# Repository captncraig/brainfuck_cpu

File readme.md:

### Main Control Signal Bus

0. CLK
1. PC_LD
2. PC_ST
3. IR_ST
4. DR_LD
5. DR_ST
6. DP_LD
7. DP_ST
8. INCREMENT_ON 
9. DECREMENT
10. ALU_LD
11. MAR_ST
12. MEM_LD
13. MEM_ST
14. MEM_PROG_DATA
15. 8Bit/16Bit

## Addional control signals

1. IO_OUT
2. IO_IN
3. IO_ACK

## FSM INPUTS

0. State0
1. State1
2. State2
3. State3
4. State4
5. DR_Z
6. IR0
7. IR1
8. IR2
9. IR_HI_Z
10. IR_LO_Z
11. RUN

## Additional FSM Outputs

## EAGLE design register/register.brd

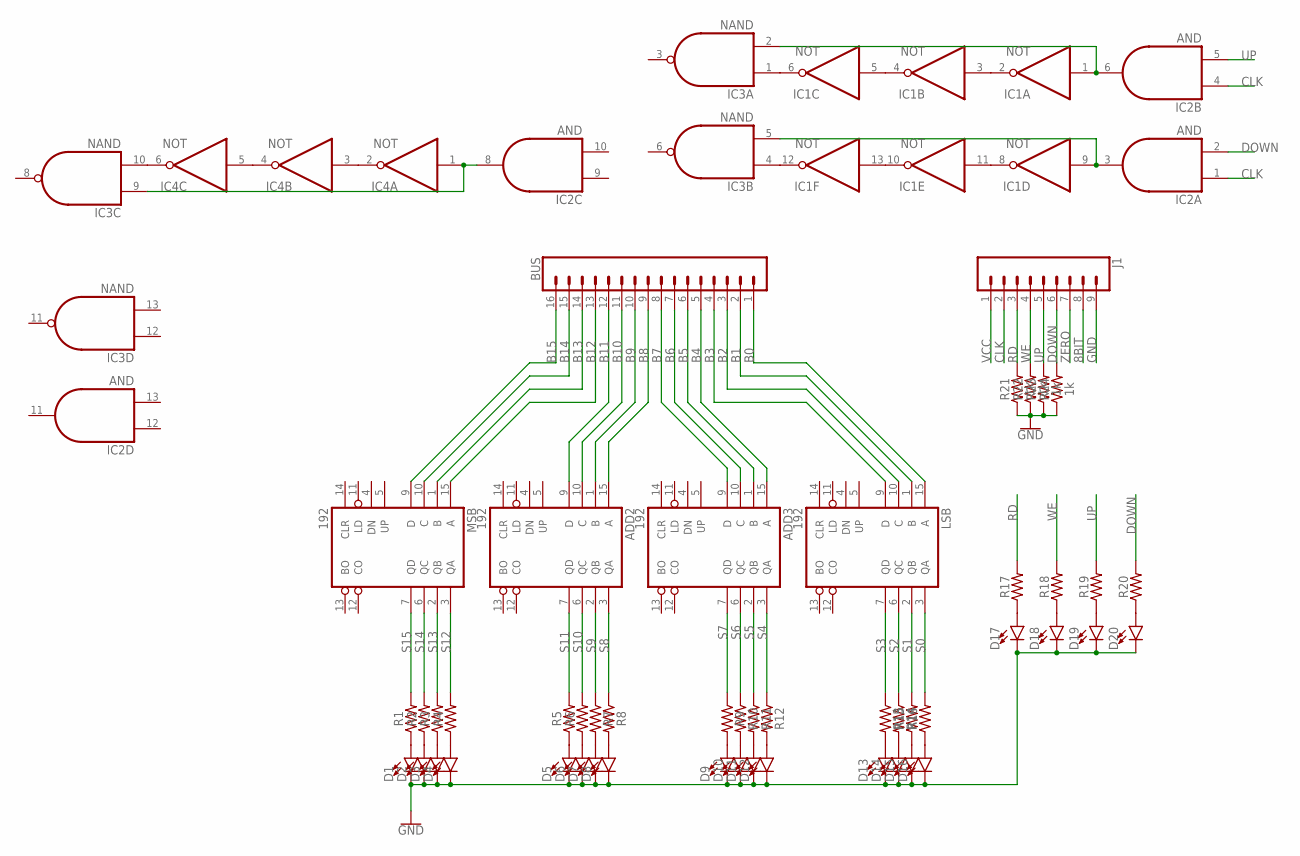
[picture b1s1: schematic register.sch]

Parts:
ADD2, ADD3: 192; DIL16
BUS: CONN_16; 1X16
D1, D2, D3, D4, D5, D6, D7, D8, D9, D10, D11, D12, D13, D14, D15, D16, D17, D18, D19, D20: LED5MM; LED_5MM
IC1, IC4: NOT; DIL14
IC2: AND; DIL14
IC3: NAND; DIL14
J1: CONN_09; 1X09
LSB: 192; DIL16
MSB: 192; DIL16
R1, R2, R3, R4, R5, R6, R7, R8, R9, R10, R11, R12, R13, R14, R15, R16, R17, R18, R19, R20: AXIAL-0.3
R21, R22, R23, R24: 1k; AXIAL-0.3

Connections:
8BIT: J1.8
B0: BUS.1, LSB.15 (A)
B1: BUS.2, LSB.1 (B)
B2: BUS.3, LSB.10 (C)
B3: BUS.4, LSB.9 (D)
B4: ADD3.15 (A), BUS.5
B5: ADD3.1 (B), BUS.6
B6: ADD3.10 (C), BUS.7
B7: ADD3.9 (D), BUS.8
B8: ADD2.15 (A), BUS.9
B9: ADD2.1 (B), BUS.10
B10: ADD2.10 (C), BUS.11
B11: ADD2.9 (D), BUS.12
B12: BUS.13, MSB.15 (A)
B13: BUS.14, MSB.1 (B)
B14: BUS.15, MSB.10 (C)
B15: BUS.16, MSB.9 (D)
CLK: IC2.1 (I0), IC2.4 (I0), J1.2
DOWN: IC2.2 (I1), J1.6, R20.P$2 (2), R24.P$2 (2)
GND: ADD2.8 (GND), ADD3.8 (GND), D1.K (C), D2.K (C), D3.K (C), D4.K (C), D5.K (C), D6.K (C), D7.K (C), D8.K (C), D9.K (C), D10.K (C), D11.K (C), D12.K (C), D13.K (C), D14.K (C), D15.K (C), D16.K (C), D17.K (C), D18.K (C), D19.K (C), D20.K (C), IC1.7 (GND), IC2.7 (GND), IC3.7 (GND), IC4.7 (GND), J1.9, LSB.8 (GND), MSB.8 (GND), R21.P$1 (1), R22.P$1 (1), R23.P$1 (1), R24.P$1 (1)
unnamed: IC1.2 (O), IC1.3 (I)
unnamed: IC1.4 (O), IC1.5 (I)
unnamed: IC1.8 (O), IC1.11 (I)
unnamed: IC1.10 (O), IC1.13 (I)
unnamed: IC1.9 (I), IC2.3 (O), IC3.5 (I1)
unnamed: IC1.1 (I), IC2.6 (O), IC3.2 (I1)
unnamed: IC1.6 (O), IC3.1 (I0)
unnamed: IC1.12 (O), IC3.4 (I0)
unnamed: IC4.2 (O), IC4.3 (I)
unnamed: IC4.4 (O), IC4.5 (I)
unnamed: IC2.8 (O), IC3.9 (I0), IC4.1 (I)
unnamed: IC3.10 (I1), IC4.6 (O)
unnamed: D1.A, R1.P$1 (1)
unnamed: D2.A, R2.P$1 (1)
unnamed: D3.A, R3.P$1 (1)
unnamed: D4.A, R4.P$1 (1)
unnamed: D5.A, R5.P$1 (1)
unnamed: D6.A, R6.P$1 (1)
unnamed: D7.A, R7.P$2 (2)
unnamed: D8.A, R8.P$2 (2)
unnamed: D9.A, R9.P$2 (2)
unnamed: D10.A, R10.P$2 (2)
unnamed: D11.A, R11.P$2 (2)
unnamed: D12.A, R12.P$2 (2)
unnamed: D13.A, R13.P$2 (2)
unnamed: D14.A, R14.P$2 (2)
unnamed: D15.A, R15.P$1 (1)
unnamed: D16.A, R16.P$1 (1)
unnamed: D18.A, R18.P$1 (1)
unnamed: D19.A, R19.P$1 (1)
unnamed: D20.A, R20.P$1 (1)
unnamed: D17.A, R17.P$1 (1)
RD: J1.3, R17.P$2 (2), R21.P$2 (2)
S0: LSB.3 (QA), R16.P$2 (2)
S1: LSB.2 (QB), R15.P$2 (2)
S2: LSB.6 (QC), R14.P$1 (1)
S3: LSB.7 (QD), R13.P$1 (1)
S4: ADD3.3 (QA), R12.P$1 (1)
S5: ADD3.2 (QB), R11.P$1 (1)
S6: ADD3.6 (QC), R10.P$1 (1)
S7: ADD3.7 (QD), R9.P$1 (1)
S8: ADD2.3 (QA), R8.P$1 (1)
S9: ADD2.2 (QB), R7.P$1 (1)
S10: ADD2.6 (QC), R6.P$2 (2)
S11: ADD2.7 (QD), R5.P$2 (2)
S12: MSB.3 (QA), R4.P$2 (2)
S13: MSB.2 (QB), R3.P$2 (2)
S14: MSB.6 (QC), R2.P$2 (2)
S15: MSB.7 (QD), R1.P$2 (2)
UP: IC2.5 (I1), J1.5, R19.P$2 (2), R23.P$2 (2)
VCC: ADD2.16 (VCC), ADD3.16 (VCC), IC1.14 (VCC), IC2.14 (VCC), IC3.14 (VCC), IC4.14 (VCC), J1.1, LSB.16 (VCC), MSB.16 (VCC)
WE: J1.4, R18.P$2 (2), R22.P$2 (2)
ZERO: J1.7

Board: 2 copper layers, 54 parts (0 on the bottom side), 71 nets, no tracks yet.

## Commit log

2022-07-18 initial

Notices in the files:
parts and their libraries:
SparkFun-Connectors: Licensing: Creative Commons ShareAlike 4.0 International - https://creativecommons.org/licenses/by-sa/4.0
